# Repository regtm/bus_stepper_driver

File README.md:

# Stepper driver motherboard for tmc5130 and raspberry pi 4
Stepper driver motherboard to control daisy chained tmc5130 stepper drivers using a raspberry pi and the drivers' spi bus interfaces.

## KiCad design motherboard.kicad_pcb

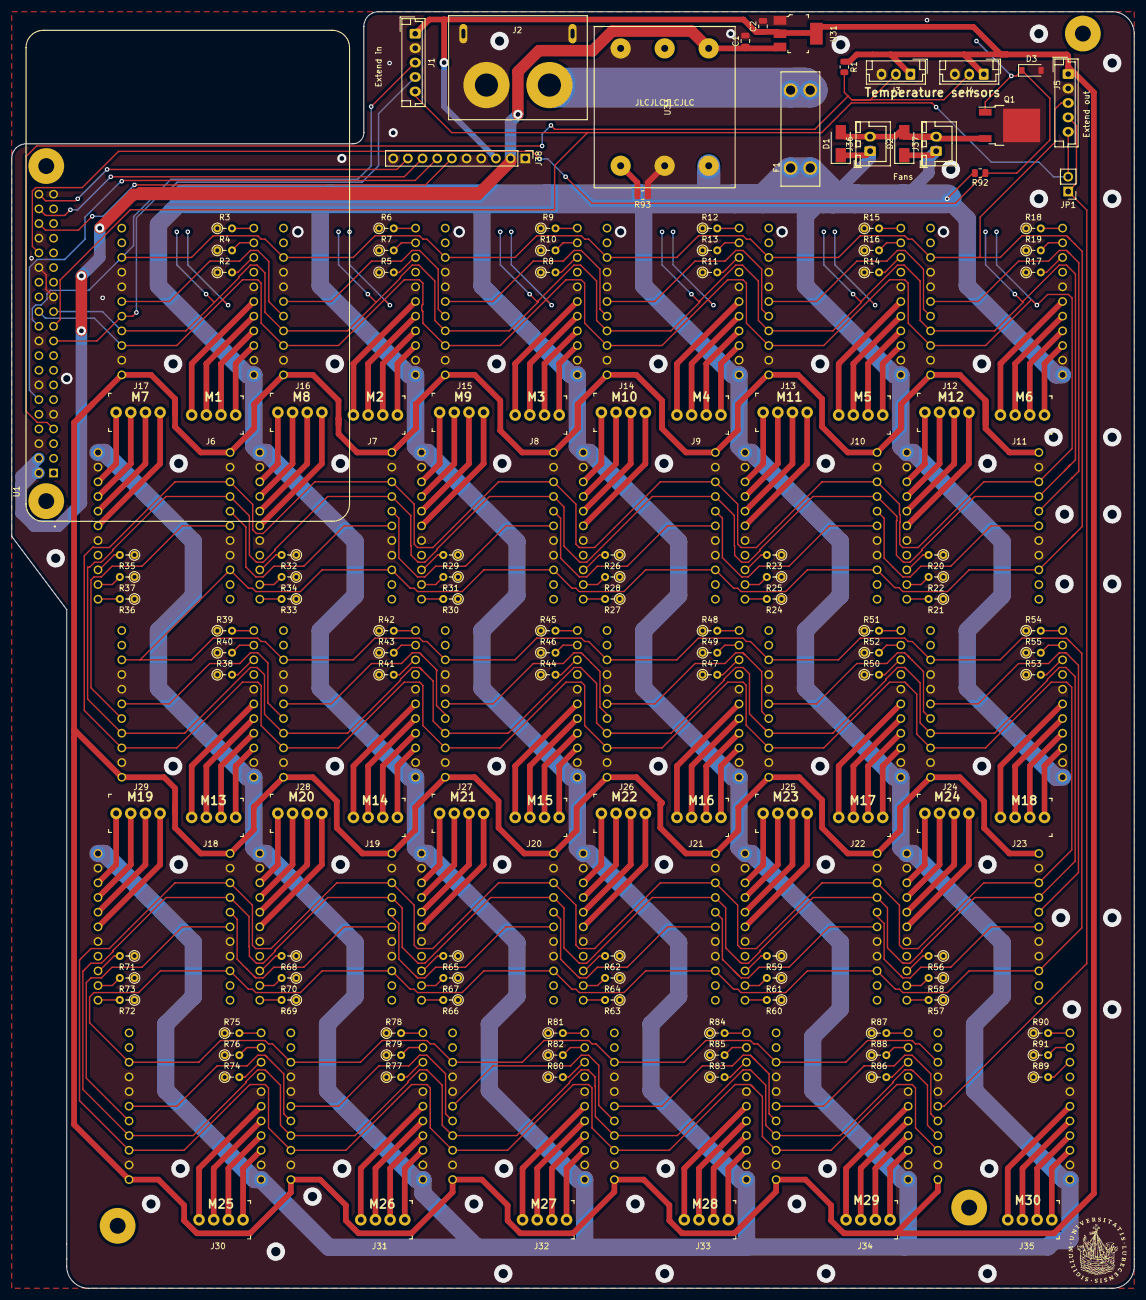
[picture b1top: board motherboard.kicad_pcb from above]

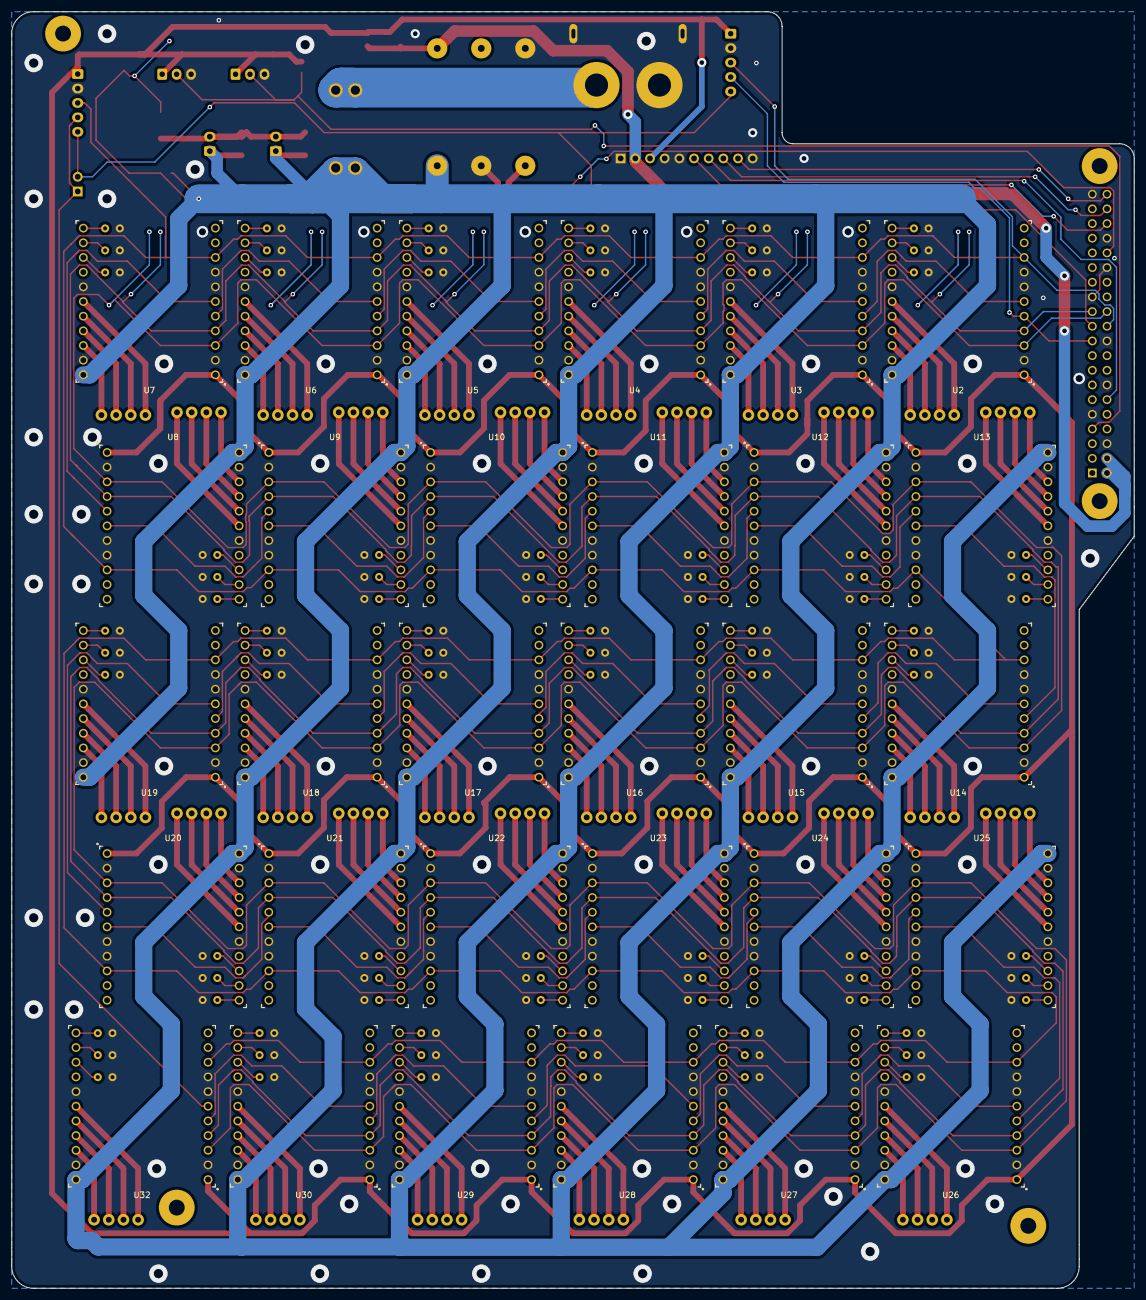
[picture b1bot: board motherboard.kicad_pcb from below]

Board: 2 copper layers, 194.3 x 221.0 mm, 173 parts (30 on the bottom side), 258 nets.

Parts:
C1: 100nf; C_0805_2012Metric
C2: 10uf; C_0805_2012Metric
D1, D2: DIODE; D_SMA
D3: 3.3v; D_SOD-123
F1: 3557-2; FUSE_3557-2
J1, J5: Conn_01x05; JST_EH_B5B-EH-A_1x05_P2.50mm_Vertical
J2: Conn_01x02; xt90pw-f
J3, J4: Conn_01x03; JST_EH_B3B-EH-A_1x03_P2.50mm_Vertical
J6, J7, J8, J9, J10, J11, J12, J13, J14, J15, J16, J17, J18, J19, J20, J21, J22, J23, J24, J25, J26, J27, J28, J29, J30, J31, J32, J33, J34, J35: 0022232041; PinHeader_1x4_P2.54mm_Drill1.02mm
J36, J37: Conn_01x02; JST_XH_B2B-XH-A_1x02_P2.50mm_Vertical
J38: Conn_01x10; PinHeader_1x10_P2.54mm_Vertical
JP1: Jumper; PinHeader_1x02_P2.54mm_Vertical
Q1: N-MOSFET; TO-252-2
R1: 4,7K; R_0805_2012Metric
R2, R3, R4, R5, R6, R7, R8, R9, R10, R11, R12, R13, R14, R15, R16, R17, R18, R19, R20, R21, R22, R23, R24, R25, R26, R27, R28, R29, R30, R31, R32, R33, R34, R35, R36, R37, R38, R39, R40, R41, R42, R43, R44, R45, R46, R47, R48, R49, R50, R51, R52, R53, R54, R55, R56, R57, R58, R59, R60, R61, R62, R63, R64, R65, R66, R67, R68, R69, R70, R71, R72, R73, R74, R75, R76, R77, R78, R79, R80, R81, R82, R83, R84, R85, R86, R87, R88, R89, R90, R91: 0; R_Axial_DIN0204_L3.6mm_D1.6mm_P2.54mm_Vertical
R92: 10k; R_0805_2012Metric
R93: 0; R_0805_2012Metric
U1: RASPBERRYPI4_4GB; MODULE_RASPBERRYPI4_4GB
U2: Logo; Uni-Luebeck
U2#2, U3, U4, U5, U6, U7, U8, U9, U10, U11, U12, U13, U14, U15, U16, U17, U18, U19, U20, U21, U22, U23, U24, U25, U26, U27, U28, U29, U30, U32: TMC5130A-BOB; 22pin1x1,1-BOB
U31: LD1117S33CTR; SOT-223
U33: SHHD003A0A41Z

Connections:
+3V3: C2.1, J1.1, J3.1, J4.1, J5.1, J38.3, R1.1, U2#2.1, U3.1, U4.1, U5.1, U6.1, U7.1, U8.1, U9.1, U10.1, U11.1, U12.1, U13.1, U14.1, U15.1, U16.1, U17.1, U18.1, U19.1, U20.1, U21.1, U22.1, U23.1, U24.1, U25.1, U26.1, U27.1, U28.1, U29.1, U30.1, U31.2, U31.4, U32.1
+5V: C1.1, J38.2, U1.2, U1.4, U31.3, U33.6
+48V: D1.1, D2.1, F1.1, F1.2, J36.1, J37.1, R92.2, U2#2.12, U3.12, U4.12, U5.12, U6.12, U7.12, U8.12, U9.12, U10.12, U11.12, U12.12, U13.12, U14.12, U15.12, U16.12, U17.12, U18.12, U19.12, U20.12, U21.12, U22.12, U23.12, U24.12, U25.12, U26.12, U27.12, U28.12, U29.12, U30.12, U32.12, U33.1
/MISO: J1.5, J5.5, JP1.2, U1.21
/MOSI: J1.4, U1.19, U2#2.5
/SW: J3.2, J4.2, R1.2, U1.7
/gpio16: J38.6, U1.36
/gpio18: J38.7, U1.12
/gpio20: J38.8, U1.38
/gpio21: J38.9, U1.40
/pwm: D3.1, Q1.1, R92.1, U1.32
/sheet5F92CD21/DATA_IN: U6.6, U7.5
/sheet5F916D5D/DATA_IN: U5.6, U6.5
/sheet5F91370A/DATA_IN: U2#2.6, U3.5
/sheet5F91474F/DATA_IN: U3.6, U4.5
/sheet5F914750/DATA_IN: U4.6, U5.5
/sheet5FAD5C7F/DATA_IN: U7.6, U8.5
/sheet5FAD5C80/DATA_IN: U8.6, U9.5
/sheet5FAD5C81/DATA_IN: U9.6, U10.5
/sheet5FAD5C82/DATA_IN: U10.6, U11.5
/sheet5FAD5C83/DATA_IN: U11.6, U12.5
/sheet5FAD5C84/DATA_IN: U12.6, U13.5
/sheet5FAD95D8/DATA_IN: U18.6, U19.5
/sheet5FAD95D9/DATA_IN: U19.6, U20.5
/sheet5FAD95DA/DATA_IN: U20.6, U21.5
/sheet5FAD95DB/DATA_IN: U21.6, U22.5
/sheet5FAD95DC/DATA_IN: U22.6, U23.5
/sheet5FAD95DD/DATA_IN: U23.6, U24.5
/sheet5FAD7671/DATA_IN: U30.6, U32.5
/sheet5FAD7671/DATA_OUT: J5.4, JP1.1, U32.6
/sheet5FAD7672/DATA_IN: U13.6, U14.5
/sheet5FAD7673/DATA_IN: U14.6, U15.5
/sheet5FAD7674/DATA_IN: U15.6, U16.5
/sheet5FAD7675/DATA_IN: U16.6, U17.5
/sheet5FAD7676/DATA_IN: U17.6, U18.5
/sheet5FADBB9A/DATA_IN: U29.6, U30.5
/sheet5FADBB95/DATA_IN: U24.6, U25.5
/sheet5FADBB96/DATA_IN: U25.6, U26.5
/sheet5FADBB97/DATA_IN: U26.6, U27.5
/sheet5FADBB98/DATA_IN: U27.6, U28.5
/sheet5FADBB99/DATA_IN: U28.6, U29.5
BUS_CLK: U1.23, U2#2.4, U3.4, U4.4, U5.4, U6.4, U7.4, U8.4, U9.4, U10.4, U11.4, U12.4, U13.4, U14.4, U15.4, U16.4, U17.4, U18.4, U19.4, U20.4, U21.4, U22.4, U23.4, U24.4, U25.4, U26.4, U27.4, U28.4, U29.4, U30.4, U32.4
CS: U1.24, U2#2.3, U3.3, U4.3, U5.3, U6.3, U7.3, U8.3, U9.3, U10.3, U11.3, U12.3, U13.3, U14.3, U15.3, U16.3, U17.3, U18.3, U19.3, U20.3, U21.3, U22.3, U23.3, U24.3, U25.3, U26.3, U27.3, U28.3, U29.3, U30.3, U32.3
EN_DRV: J1.3, J5.3, U1.22, U2#2.9, U3.9, U4.9, U5.9, U6.9, U7.9, U8.9, U9.9, U10.9, U11.9, U12.9, U13.9, U14.9, U15.9, U16.9, U17.9, U18.9, U19.9, U20.9, U21.9, U22.9, U23.9, U24.9, U25.9, U26.9, U27.9, U28.9, U29.9, U30.9, U32.9
GND: C1.2, C2.2, D3.2, J1.2, J2.2, J2.3, J2.4, J3.3, J4.3, J5.2, J38.1, J38.4, J38.5, J38.10, Q1.2, R2.1, R3.1, R4.1, R5.1, R6.1, R7.1, R8.1, R9.1, R10.1, R11.1, R12.1, R13.1, R14.1, R15.1, R16.1, R17.1, R18.1, R19.1, R20.1, R21.1, R22.1, R23.1, R24.1, R25.1, R26.1, R27.1, R28.1, R29.1, R30.1, R31.1, R32.1, R33.1, R34.1, R35.1, R36.1, R37.1, R38.1, R39.1, R40.1, R41.1, R42.1, R43.1, R44.1, R45.1, R46.1, R47.1, R48.1, R49.1, R50.1, R51.1, R52.1, R53.1, R54.1, R55.1, R56.1, R57.1, R58.1, R59.1, R60.1, R61.1, R62.1, R63.1, R64.1, R65.1, R66.1, R67.1, R68.1, R69.1, R70.1, R71.1, R72.1, R73.1, R74.1, R75.1, R76.1, R77.1, R78.1, R79.1, R80.1, R81.1, R82.1, R83.1, R84.1, R85.1, R86.1, R87.1, R88.1, R89.1, R90.1, R91.1, R93.1, U1.6, U1.9, U1.14, U1.20, U1.25, U1.30, U1.34, U1.39, U2#2.2, U2#2.7, U2#2.8, U2#2.13, U2#2.18, U3.2, U3.7, U3.8, U3.13, U3.18, U4.2, U4.7, U4.8, U4.13, U4.18, U5.2, U5.7, U5.8, U5.13, U5.18, U6.2, U6.7, U6.8, U6.13, U6.18, U7.2, U7.7, U7.8, U7.13, U7.18, U8.2, U8.7, U8.8, U8.13, U8.18, U9.2, U9.7, U9.8, U9.13, U9.18, U10.2, U10.7, U10.8, U10.13, U10.18, U11.2, U11.7, U11.8, U11.13, U11.18, U12.2, U12.7, U12.8, U12.13, U12.18, U13.2, U13.7, U13.8, U13.13, U13.18, U14.2, U14.7, U14.8, U14.13, U14.18, U15.2, U15.7, U15.8, U15.13, U15.18, U16.2, U16.7, U16.8, U16.13, U16.18, U17.2, U17.7, U17.8, U17.13, U17.18, U18.2, U18.7, U18.8, U18.13, U18.18, U19.2, U19.7, U19.8, U19.13, U19.18, U20.2, U20.7, U20.8, U20.13, U20.18, U21.2, U21.7, U21.8, U21.13, U21.18, U22.2, U22.7, U22.8, U22.13, U22.18, U23.2, U23.7, U23.8, U23.13, U23.18, U24.2, U24.7, U24.8, U24.13, U24.18, U25.2, U25.7, U25.8, U25.13, U25.18, U26.2, U26.7, U26.8, U26.13, U26.18, U27.2, U27.7, U27.8, U27.13, U27.18, U28.2, U28.7, U28.8, U28.13, U28.18, U29.2, U29.7, U29.8, U29.13, U29.18, U30.2, U30.7, U30.8, U30.13, U30.18, U31.1, U32.2, U32.7, U32.8, U32.13, U32.18, U33.2, U33.4
unnamed: D1.2, D2.2, J36.2, J37.2, Q1.3
unnamed: F1.3, F1.4, J2.1
unnamed: J6.1, U2#2.14
unnamed: J6.2, U2#2.15
unnamed: J6.3, U2#2.16
unnamed: J6.4, U2#2.17
unnamed: J7.1, U3.14
unnamed: J7.2, U3.15
unnamed: J7.3, U3.16
unnamed: J7.4, U3.17
unnamed: J8.1, U4.14
unnamed: J8.2, U4.15
unnamed: J8.3, U4.16
unnamed: J8.4, U4.17
unnamed: J9.1, U5.14
unnamed: J9.2, U5.15
unnamed: J9.3, U5.16
unnamed: J9.4, U5.17
unnamed: J10.1, U6.14
unnamed: J10.2, U6.15
unnamed: J10.3, U6.16
unnamed: J10.4, U6.17
unnamed: J11.1, U7.14
unnamed: J11.2, U7.15
unnamed: J11.3, U7.16
unnamed: J11.4, U7.17
unnamed: J12.1, U8.14
unnamed: J12.2, U8.15
unnamed: J12.3, U8.16
unnamed: J12.4, U8.17
unnamed: J13.1, U9.14
unnamed: J13.2, U9.15
unnamed: J13.3, U9.16
unnamed: J13.4, U9.17
unnamed: J14.1, U10.14
unnamed: J14.2, U10.15
unnamed: J14.3, U10.16
unnamed: J14.4, U10.17
unnamed: J15.1, U11.14
unnamed: J15.2, U11.15
unnamed: J15.3, U11.16
unnamed: J15.4, U11.17
unnamed: J16.1, U12.14
unnamed: J16.2, U12.15
unnamed: J16.3, U12.16
unnamed: J16.4, U12.17
unnamed: J17.1, U13.14
unnamed: J17.2, U13.15
unnamed: J17.3, U13.16
unnamed: J17.4, U13.17
unnamed: J18.1, U14.14
unnamed: J18.2, U14.15
unnamed: J18.3, U14.16
unnamed: J18.4, U14.17
unnamed: J19.1, U15.14
unnamed: J19.2, U15.15
unnamed: J19.3, U15.16
unnamed: J19.4, U15.17
unnamed: J20.1, U16.14
unnamed: J20.2, U16.15
unnamed: J20.3, U16.16
unnamed: J20.4, U16.17
unnamed: J21.1, U17.14
unnamed: J21.2, U17.15
unnamed: J21.3, U17.16
unnamed: J21.4, U17.17
unnamed: J22.1, U18.14
unnamed: J22.2, U18.15
unnamed: J22.3, U18.16
unnamed: J22.4, U18.17
unnamed: J23.1, U19.14
unnamed: J23.2, U19.15
unnamed: J23.3, U19.16
unnamed: J23.4, U19.17
unnamed: J24.1, U20.14
unnamed: J24.2, U20.15
unnamed: J24.3, U20.16
unnamed: J24.4, U20.17
unnamed: J25.1, U21.14
unnamed: J25.2, U21.15
unnamed: J25.3, U21.16
unnamed: J25.4, U21.17
unnamed: J26.1, U22.14
unnamed: J26.2, U22.15
unnamed: J26.3, U22.16
unnamed: J26.4, U22.17
unnamed: J27.1, U23.14
unnamed: J27.2, U23.15
unnamed: J27.3, U23.16
unnamed: J27.4, U23.17
unnamed: J28.1, U24.14
unnamed: J28.2, U24.15
unnamed: J28.3, U24.16
unnamed: J28.4, U24.17
unnamed: J29.1, U25.14
unnamed: J29.2, U25.15
unnamed: J29.3, U25.16
unnamed: J29.4, U25.17
unnamed: J30.1, U26.14
unnamed: J30.2, U26.15
unnamed: J30.3, U26.16
unnamed: J30.4, U26.17
unnamed: J31.1, U27.14
unnamed: J31.2, U27.15
unnamed: J31.3, U27.16
unnamed: J31.4, U27.17
unnamed: J32.1, U28.14
unnamed: J32.2, U28.15
unnamed: J32.3, U28.16
unnamed: J32.4, U28.17
unnamed: J33.1, U29.14
unnamed: J33.2, U29.15
unnamed: J33.3, U29.16
unnamed: J33.4, U29.17
unnamed: J34.1, U30.14
unnamed: J34.2, U30.15
unnamed: J34.3, U30.16
unnamed: J34.4, U30.17
unnamed: J35.1, U32.14
unnamed: J35.2, U32.15
unnamed: J35.3, U32.16
unnamed: J35.4, U32.17
unnamed: R2.2, U2#2.20
unnamed: R3.2, U2#2.22
unnamed: R4.2, U2#2.21
unnamed: R5.2, U3.20
unnamed: R6.2, U3.22
unnamed: R7.2, U3.21
unnamed: R8.2, U4.20
unnamed: R9.2, U4.22
unnamed: R10.2, U4.21
unnamed: R11.2, U5.20
unnamed: R12.2, U5.22
unnamed: R13.2, U5.21
unnamed: R14.2, U6.20
unnamed: R15.2, U6.22
unnamed: R16.2, U6.21
unnamed: R17.2, U7.20
unnamed: R18.2, U7.22
unnamed: R19.2, U7.21
unnamed: R20.2, U8.20
unnamed: R21.2, U8.22
unnamed: R22.2, U8.21
unnamed: R23.2, U9.20
unnamed: R24.2, U9.22
unnamed: R25.2, U9.21
unnamed: R26.2, U10.20
unnamed: R27.2, U10.22
unnamed: R28.2, U10.21
unnamed: R29.2, U11.20
unnamed: R30.2, U11.22
unnamed: R31.2, U11.21
unnamed: R32.2, U12.20
unnamed: R33.2, U12.22
unnamed: R34.2, U12.21
unnamed: R35.2, U13.20
unnamed: R36.2, U13.22
unnamed: R37.2, U13.21
unnamed: R38.2, U14.20
unnamed: R39.2, U14.22
unnamed: R40.2, U14.21
unnamed: R41.2, U15.20
unnamed: R42.2, U15.22
unnamed: R43.2, U15.21
unnamed: R44.2, U16.20
unnamed: R45.2, U16.22
unnamed: R46.2, U16.21
unnamed: R47.2, U17.20
unnamed: R48.2, U17.22
unnamed: R49.2, U17.21
unnamed: R50.2, U18.20
unnamed: R51.2, U18.22
unnamed: R52.2, U18.21
unnamed: R53.2, U19.20
unnamed: R54.2, U19.22
unnamed: R55.2, U19.21
unnamed: R56.2, U20.20
unnamed: R57.2, U20.22
unnamed: R58.2, U20.21
unnamed: R59.2, U21.20
unnamed: R60.2, U21.22
unnamed: R61.2, U21.21
unnamed: R62.2, U22.20
unnamed: R63.2, U22.22
unnamed: R64.2, U22.21
unnamed: R65.2, U23.20
unnamed: R66.2, U23.22
unnamed: R67.2, U23.21
unnamed: R68.2, U24.20
unnamed: R69.2, U24.22
unnamed: R70.2, U24.21
unnamed: R71.2, U25.20
unnamed: R72.2, U25.22
unnamed: R73.2, U25.21
unnamed: R74.2, U26.20
unnamed: R75.2, U26.22
unnamed: R76.2, U26.21
unnamed: R77.2, U27.20
unnamed: R78.2, U27.22
unnamed: R79.2, U27.21
unnamed: R80.2, U28.20
unnamed: R81.2, U28.22
unnamed: R82.2, U28.21
unnamed: R83.2, U29.20
unnamed: R84.2, U29.22
unnamed: R85.2, U29.21
unnamed: R86.2, U30.20
unnamed: R87.2, U30.22
unnamed: R88.2, U30.21
unnamed: R89.2, U32.20
unnamed: R90.2, U32.22
unnamed: R91.2, U32.21
unnamed: R93.2, U33.3

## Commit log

2022-01-18 add schematics picture for readme
